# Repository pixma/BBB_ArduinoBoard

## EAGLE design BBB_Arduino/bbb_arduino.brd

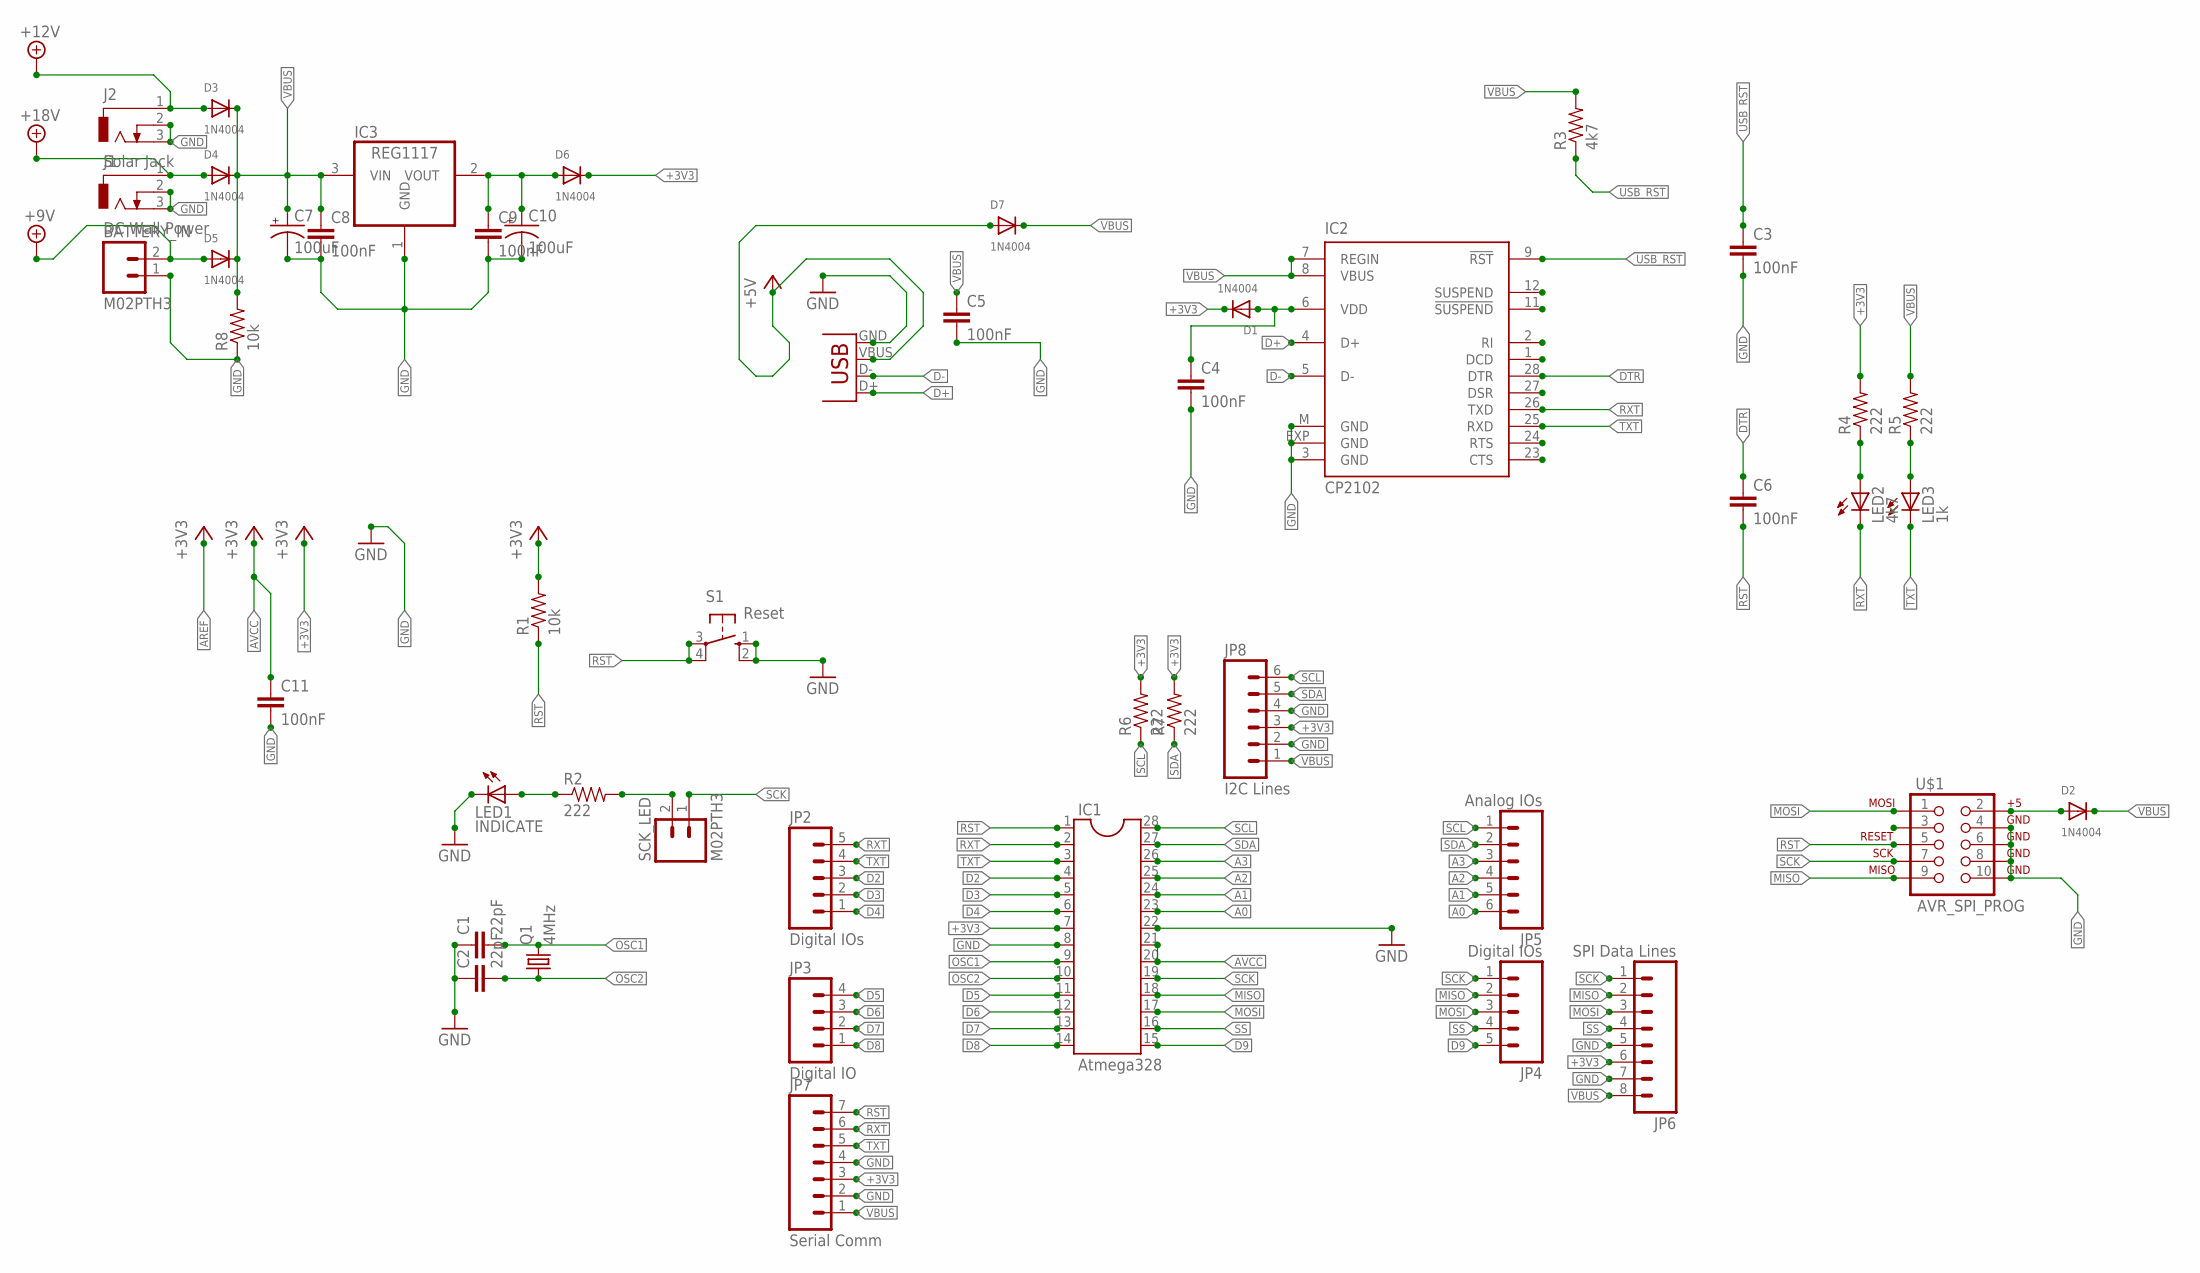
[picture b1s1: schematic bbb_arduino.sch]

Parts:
BATTERY_IN: M02PTH3; 1X02_LONGPADS
C1, C2: 22pF; 1206
C3, C4, C5, C6, C8, C9, C11: 100nF; 1206
C7, C10: 100uF; CPOL-RADIAL-100UF-25V
D1, D2, D3, D4, D5, D6, D7: 1N4004; SMADIODE
IC1: Atmega328; DIL28-3
IC2: CP2102; MLP28
IC3: REG1117; SOT223
J1: DC Wall Power; DCJ0303
J2: Solar Jack; DCJ0303
JP1: USB-SMD-NS; USB-MINIB-NOSTOP
JP2, JP4: Digital IOs; 1X05_LONGPADS
JP3: Digital IO; 1X04_LONGPADS
JP5: Analog IOs; 1X06_LONGPADS
JP6: SPI Data Lines; 1X08_LONGPADS
JP7: Serial Comm; 1X07_LONGPADS
JP8: I2C Lines; 1X06_LONGPADS
LED1: INDICATE; CHIPLED_1206
LED2: 4k7; CHIPLED_1206
LED3: 1k; CHIPLED_1206
Q1: 4MHz; HC49/S
R1, R8: 10k; 1206
R2, R4, R5, R6, R7: 222; 1206
R3: 4k7; 1206
S1: Reset; B3F-10XX
SCK_LED: M02PTH3; 1X02_LONGPADS
U$1: AVR_SPI_PROG; AVR_ICSP

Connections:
+3V3: D1.C, D6.C, IC1.7, JP6.6, JP7.3, JP8.3, R1.2, R4.2, R6.2, R7.2
+5V: D7.A, JP1.VBUS
+9V: BATTERY_IN.2, D5.A
+12V: D3.A, J2.1
+18V: D4.A, J1.1
A0: IC1.23, JP5.6
A1: IC1.24, JP5.5
A2: IC1.25, JP5.4
A3: IC1.26, JP5.3
AVCC: C11.1, IC1.20, IC1.21
D2: IC1.4, JP2.3
D3: IC1.5, JP2.2
D4: IC1.6, JP2.1
D5: IC1.11, JP3.4
D6: IC1.12, JP3.3
D7: IC1.13, JP3.2
D8: IC1.14, JP3.1
D9: IC1.15, JP4.5
D+: IC2.4 (D+), JP1.D+
D-: IC2.5 (D-), JP1.D-
DTR: C6.1, IC2.28 (DTR)
GND: BATTERY_IN.1, C1.1, C2.1, C3.2, C4.2, C5.2, C7.2 (-), C8.2, C9.2, C10.2 (-), C11.2, IC1.8, IC1.22, IC2.3 (GND), IC2.EXP (GND), IC2.M (GND), IC3.1 (GND), J1.2, J1.3, J2.2, J2.3, JP1.GND, JP6.5, JP6.7, JP7.2, JP7.4, JP8.2, JP8.4, LED1.C, R8.1, S1.1 (S), S1.2 (S1), U$1.4, U$1.6, U$1.8, U$1.10
MISO: IC1.18, JP4.2, JP6.2, U$1.9
MOSI: IC1.17, JP4.3, JP6.3, U$1.1
unnamed: LED1.A, R2.1
unnamed: R2.2, SCK_LED.2
unnamed: LED2.A, R4.1
unnamed: C4.1, D1.A, IC2.6 (VDD)
unnamed: LED3.A, R5.1
unnamed: D2.A, U$1.2
unnamed: C9.1, C10.1 (+), D6.A, IC3.2 (VOUT)
OSC1: C1.2, IC1.9, Q1.2
OSC2: C2.2, IC1.10, Q1.1
RST: C6.2, IC1.1, JP7.7, R1.1, S1.3, S1.4 (P1), U$1.5
RXT: IC1.2, IC2.26 (TXD), JP2.5, JP7.6, LED2.C
SCK: IC1.19, JP4.1, JP6.1, SCK_LED.1, U$1.7
SCL: IC1.28, JP5.1, JP8.6, R6.1
SDA: IC1.27, JP5.2, JP8.5, R7.1
SS: IC1.16, JP4.4, JP6.4
TXT: IC1.3, IC2.25 (RXD), JP2.4, JP7.5, LED3.C
USB_RST: C3.1, IC2.9 (!RST), R3.1
VBUS: C5.1, C7.1 (+), C8.1, D2.C, D3.C, D4.C, D5.C, D7.C, IC2.7 (REGIN), IC2.8 (VBUS), IC3.3 (VIN), JP6.8, JP7.1, JP8.1, R3.2, R5.2, R8.2

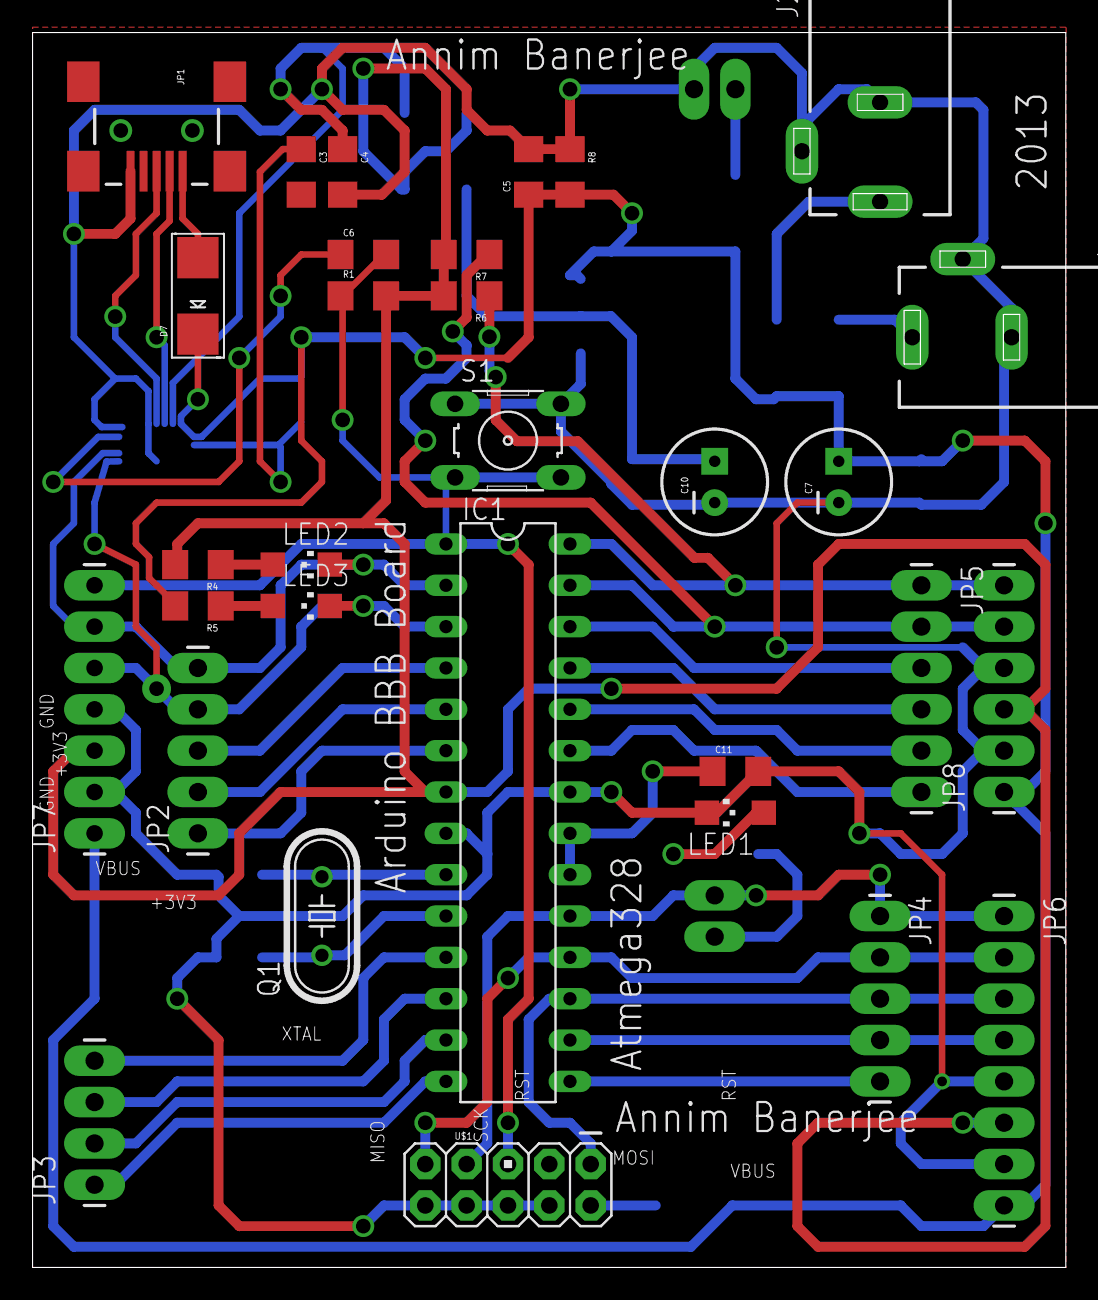
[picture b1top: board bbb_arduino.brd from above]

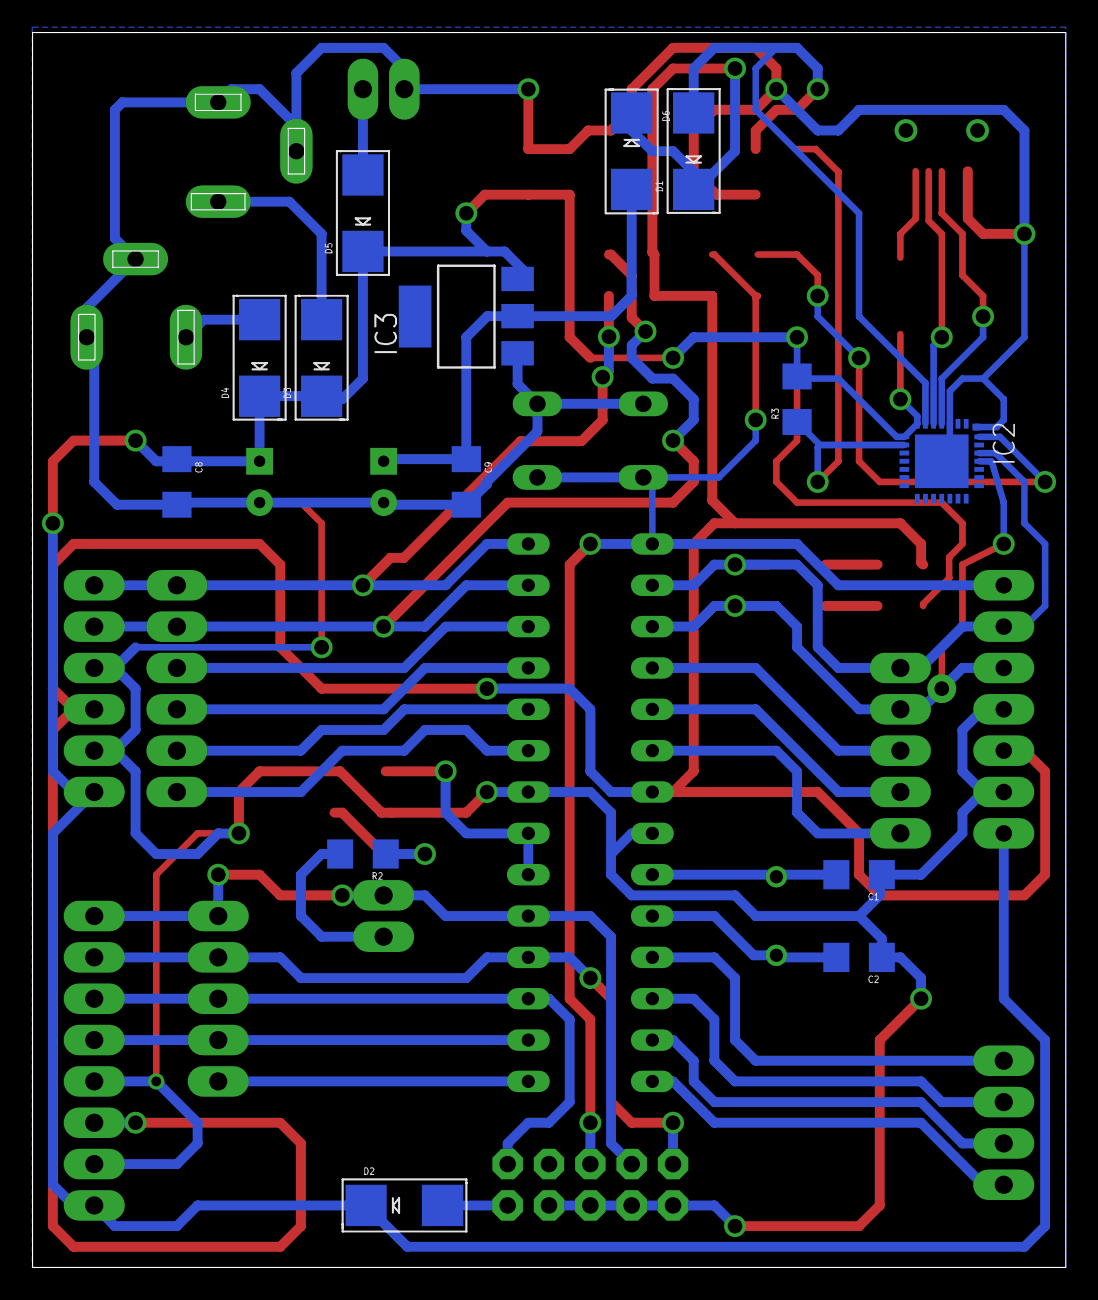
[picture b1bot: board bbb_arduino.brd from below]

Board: 2 copper layers, 63.5 x 75.9 mm, 47 parts (14 on the bottom side), 42 nets.

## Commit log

2013-12-11 new gerber files released
2013-12-25 untracked files are updated, random

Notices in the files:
parts and their libraries:
SparkFun-Resistors: Licensing: CC v3.0 Share-Alike You are welcome to use this library for commercial purposes.
